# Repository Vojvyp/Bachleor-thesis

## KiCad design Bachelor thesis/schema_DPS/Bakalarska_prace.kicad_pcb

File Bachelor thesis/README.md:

# Bachelor thesis
Repository of my Bachelor thesis 2021

&nbsp;
Téma: Měřící přípravek pulzů srdce pomocí PPG snímače
&nbsp;

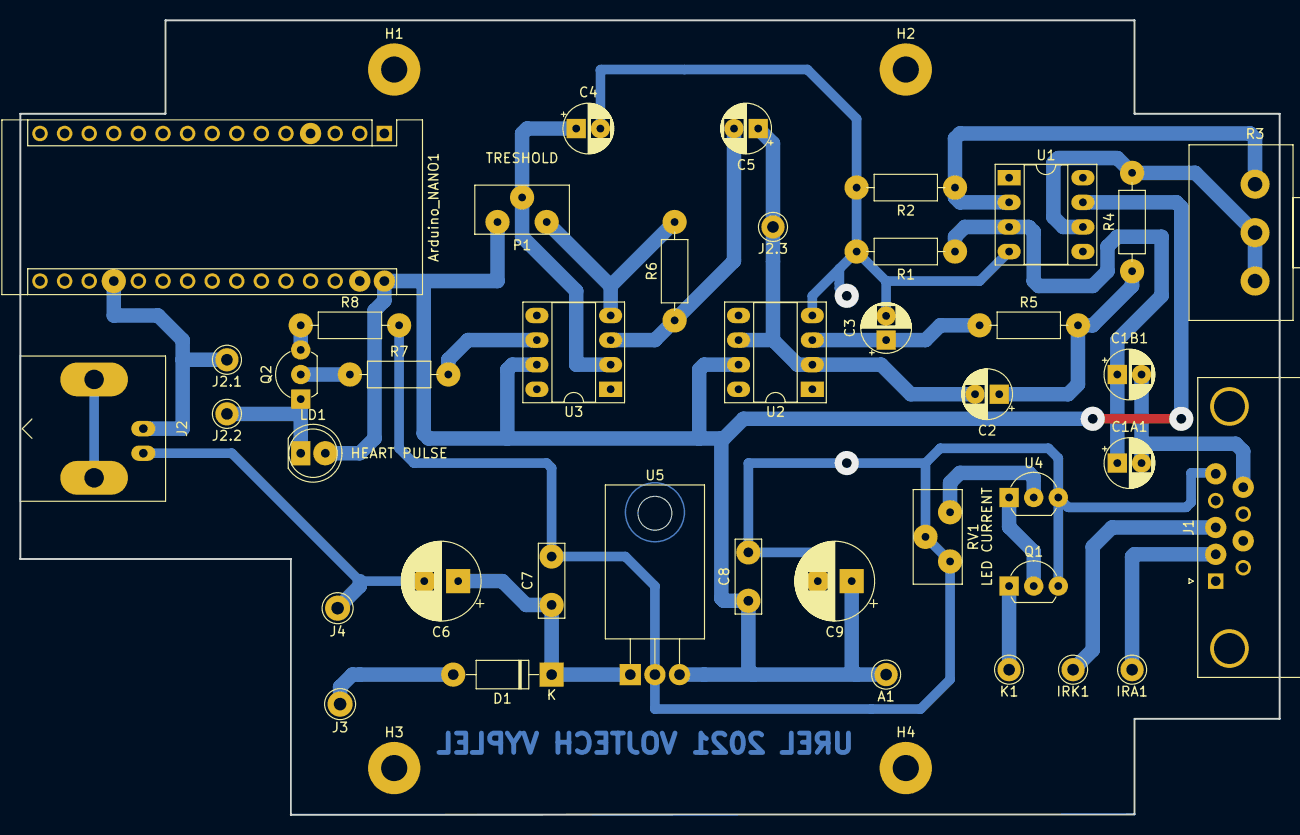
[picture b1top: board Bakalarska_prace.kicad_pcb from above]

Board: 2 copper layers, 130.0 x 82.0 mm, 45 parts (0 on the bottom side), 23 nets.

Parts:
A1: Conn_01x01_Female; Pin_D1.0mm_L10.0mm_LooseFit
Arduino_NANO1: Arduino_Nano_Every; Arduino_Nano
C1A1, C1B1, C4: 4.7u; CP_Radial_D5.0mm_P2.50mm
C2, C3: 22u; CP_Radial_D5.0mm_P2.50mm
C5: 1u; CP_Radial_D5.0mm_P2.50mm
C6, C9: 100u; CP_Radial_D8.0mm_P3.50mm
C7, C8: 100n; C_Disc_D7.5mm_W2.5mm_P5.00mm
D1: 1N4007; D_DO-41_SOD81_P10.16mm_Horizontal
H1, H2, H3, H4: MountingHole; MountingHole_2.7mm_Pad
IRA1: Conn_01x01_Female; Pin_D1.0mm_L10.0mm_LooseFit
IRK1: Conn_01x01_Female; Pin_D1.0mm_L10.0mm_LooseFit
J1: DB9; DSUB-9_Male_Horizontal_P2.77x2.84mm_EdgePinOffset7.70mm_Hou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
J2: BNC; BNC_Amphenol_B6252HB-NPP3G-50_Horizontal
J2.1, J2.2, J2.3: Conn_01x01_Female; Pin_D1.0mm_L10.0mm_LooseFit
J3: +; Pin_D1.3mm_L11.0mm
J4: -; Pin_D1.3mm_L11.0mm
K1: Conn_01x01_Female; Pin_D1.0mm_L10.0mm_LooseFit
LD1: GREEN LED; LED_D5.0mm_Clear
P1: 50k; Potentiometer_Bourns_3296Y_Vertical
Q1: BC557; TO-92L_Inline_Wide
Q2: BC337; TO-92L_Inline_Wide
R1, R6: 100k; R_Axial_DIN0207_L6.3mm_D2.5mm_P10.16mm_Horizontal_Standard
R2, R4, R5: 1k; R_Axial_DIN0207_L6.3mm_D2.5mm_P10.16mm_Horizontal_Standard
R3: 1M; Potentiometer_Alps_RK163_Single_Horizontal
R7: 120R; R_Axial_DIN0207_L6.3mm_D2.5mm_P10.16mm_Horizontal_Standard
R8: 220; R_Axial_DIN0207_L6.3mm_D2.5mm_P10.16mm_Horizontal_Standard
RV1: 4.7k; Potentiometer_Bourns_3296Y_Vertical
U1: CA3140; DIP-8_W7.62mm_Socket_LongPads
U2, U3: MCP601; DIP-8_W7.62mm_Socket_LongPads
U4: LM334SM; LM334_TO92
U5: L7805; TO-220-3_Horizontal_TabDown

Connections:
+5V: A1.1, Arduino_NANO1.30, C8.1, C9.1, LD1.2, P1.1, U1.7, U2.7, U3.7, U5.3
GNDD: Arduino_NANO1.4, Arduino_NANO1.29, C3.2, C4.2, C6.2, C7.2, C8.2, C9.2, J1.5, J1.7, J2.2, J4.1, P1.3, Q1.3, R1.2, R2.2, R6.2, R8.2, RV1.1, RV1.2, U1.4, U2.4, U3.4, U4.1, U5.2
unnamed: Arduino_NANO1.19, J2.1, J2.1.1
unnamed: C1A1.1, C1B1.1, R1.1, U1.3
unnamed: C1A1.2, C1B1.2, J1.9
unnamed: C2.1, R4.1, R5.2
unnamed: C2.2, C5.1, J2.3.1, U2.2, U2.6
unnamed: C3.1, R5.1, U2.3
unnamed: C4.1, P1.2, U3.2
unnamed: C5.2, R6.1, U3.3
unnamed: C6.1, C7.1, D1.1, U5.1
unnamed: D1.2, J3.1
unnamed: IRA1.1, J1.2
unnamed: IRK1.1, J1.3
unnamed: J2.2.1, LD1.1, Q2.1
unnamed: K1.1, Q1.1
unnamed: Q1.2, U4.3
unnamed: Q2.2, R7.1
unnamed: Q2.3, R8.1
unnamed: R2.1, R3.3, U1.2
unnamed: R3.1, R3.2, R4.2, U1.6
unnamed: R7.2, U3.6
unnamed: RV1.3, U4.2

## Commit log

2021-03-12 upload
